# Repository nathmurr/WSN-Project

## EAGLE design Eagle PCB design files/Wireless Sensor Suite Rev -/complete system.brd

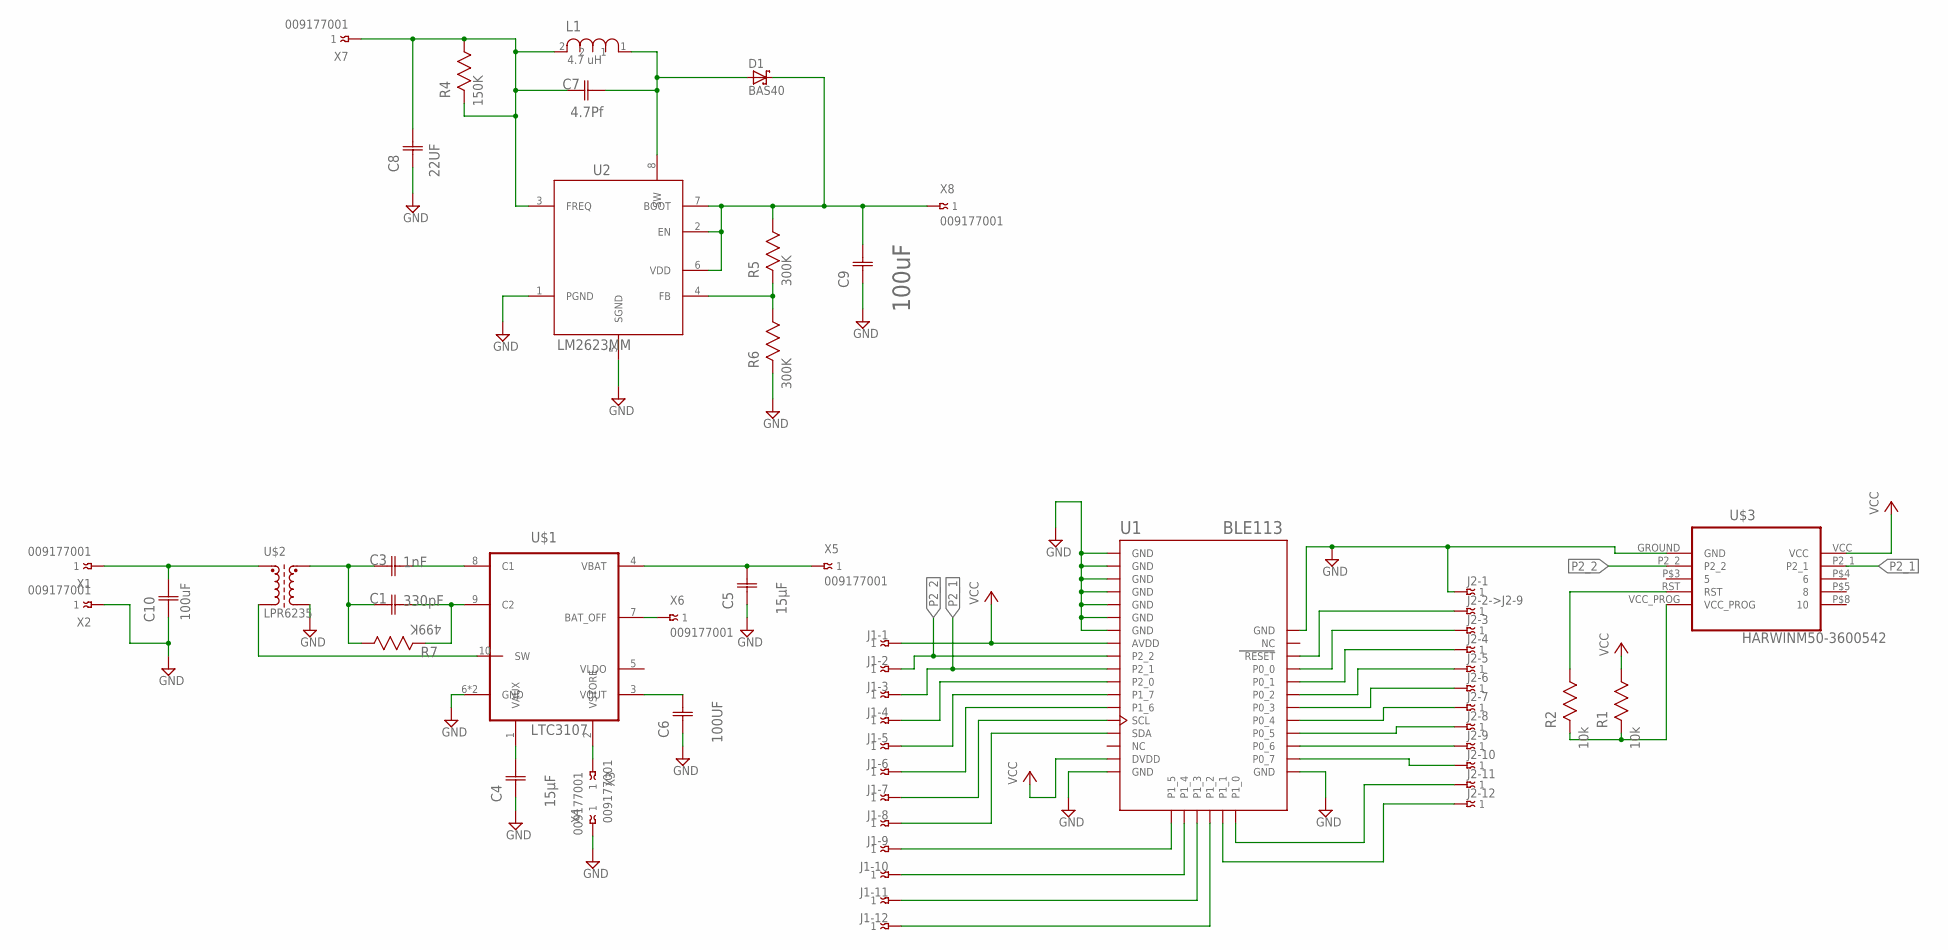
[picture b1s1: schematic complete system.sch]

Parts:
C1: 330pF; CAPC1005X60N
C3: 1nF; CAPC1005X60N
C4, C5: 15µF; CAPCP3216X180N
C6: 100UF; CAPCP3216X180N
C7: 4.7Pf; CAPC1005X60N
C8: 22UF; CAPC2012X94N
C9, C10: 100uF; CAPC3216X180N
D1: BAS40; SOT23
J1-1, J1-2, J1-3, J1-4, J1-5, J1-6, J1-7, J1-8, J1-9, J1-10, J1-11, J1-12, J2-1, J2-2->J2-9, J2-3, J2-4, J2-5, J2-6, J2-7, J2-8, J2-9, J2-10, J2-11, J2-12: 009177001
L1: 4.7 uH; INDC3225X22N
R1, R2: 10k; RESC1005X40N
R4: 150K; RESC1005X40N
R5, R6: 300K; RESC1005X40N
R7: 499K; RESC1005X40N
U1: BLE113; BLE113-A
U2: LM2623MM; SOP65P490X110-8N
U$1: LTC3107
U$2: LPR6235
U$3: HARWINM50-3600542
X1, X2, X3, X4, X5, X6, X7, X8: 009177001

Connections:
GND: C4.1 (C1), C5.1 (C1), C6.1 (C1), C8.1 (C1), C9.1 (C1), C10.1 (C1), J2-1.1, R6.2, U1.GND, U1.GND@2 (GND), U1.GND@3 (GND), U1.GND@4 (GND), U1.GND@5 (GND), U1.GND@6 (GND), U1.GND@7 (GND), U1.GND@8 (GND), U1.GND@9 (GND), U1.GND@10 (GND), U2.1 (PGND), U2.5 (SGND), U$1.6 (GND), U$1.11 (GND), U$2.P$3 (OP2), U$3.GROUND (GND), X2.1, X4.1
LL: J2-11.1, U1.P1_0
unnamed: C10.2 (C2), U$2.P$1 (IP1), X1.1
unnamed: U$1.10 (SW), U$2.P$2 (IP2)
unnamed: C1.1 (C2), R7.2, U$1.9 (C2)
unnamed: C1.2 (C1), C3.2 (C1), R7.1, U$2.P$4 (OP1)
unnamed: C3.1 (C2), U$1.8 (C1)
unnamed: C4.2 (C2), U$1.1 (VAUX)
unnamed: U$1.2 (VSTORE), X3.1
unnamed: C5.2 (C2), U$1.4 (VBAT), X5.1
unnamed: U$1.7 (BAT_OFF), X6.1
unnamed: C6.2 (C2), U$1.3 (VOUT)
unnamed: R1.2, R2.2, U$3.VCC_PROG
unnamed: R2.1, U$3.RST
unnamed: J1-4.1, U1.P2_0
unnamed: J1-5.1, U1.P1_7
unnamed: J1-6.1, U1.P1_6
unnamed: J1-7.1, U1.SCL
unnamed: J1-8.1, U1.SDA
unnamed: J1-9.1, U1.P1_5
unnamed: J1-10.1, U1.P1_4
unnamed: J1-11.1, U1.P1_3
unnamed: J1-12.1, U1.P1_2
unnamed: J2-3.1, U1.P0_0
unnamed: J2-4.1, U1.P0_1
unnamed: J2-2->J2-9.1, U1.RESET
unnamed: J2-5.1, U1.P0_2
unnamed: J2-6.1, U1.P0_3
unnamed: J2-7.1, U1.P0_4
unnamed: J2-8.1, U1.P0_5
unnamed: J2-9.1, U1.P0_6
unnamed: J2-10.1, U1.P0_7
unnamed: C7.1 (C2), D1.1 (A), L1.1, U2.8 (SW)
unnamed: J2-12.1, U1.P1_1
unnamed: C7.2 (C1), C8.2 (C2), L1.2, R4.1, R4.2, U2.3 (FREQ), X7.1
unnamed: C9.2 (C2), D1.3 (C), R5.1, U2.2 (EN), U2.6 (VDD), U2.7 (BOOT), X8.1
unnamed: R5.2, R6.1, U2.4 (FB)
P2_1: J1-3.1, U1.P2_1, U$3.P2_1
P2_2: J1-2.1, U1.P2_2, U$3.P2_2
VCC: J1-1.1, R1.1, U1.AVDD, U1.DVDD, U$3.VCC

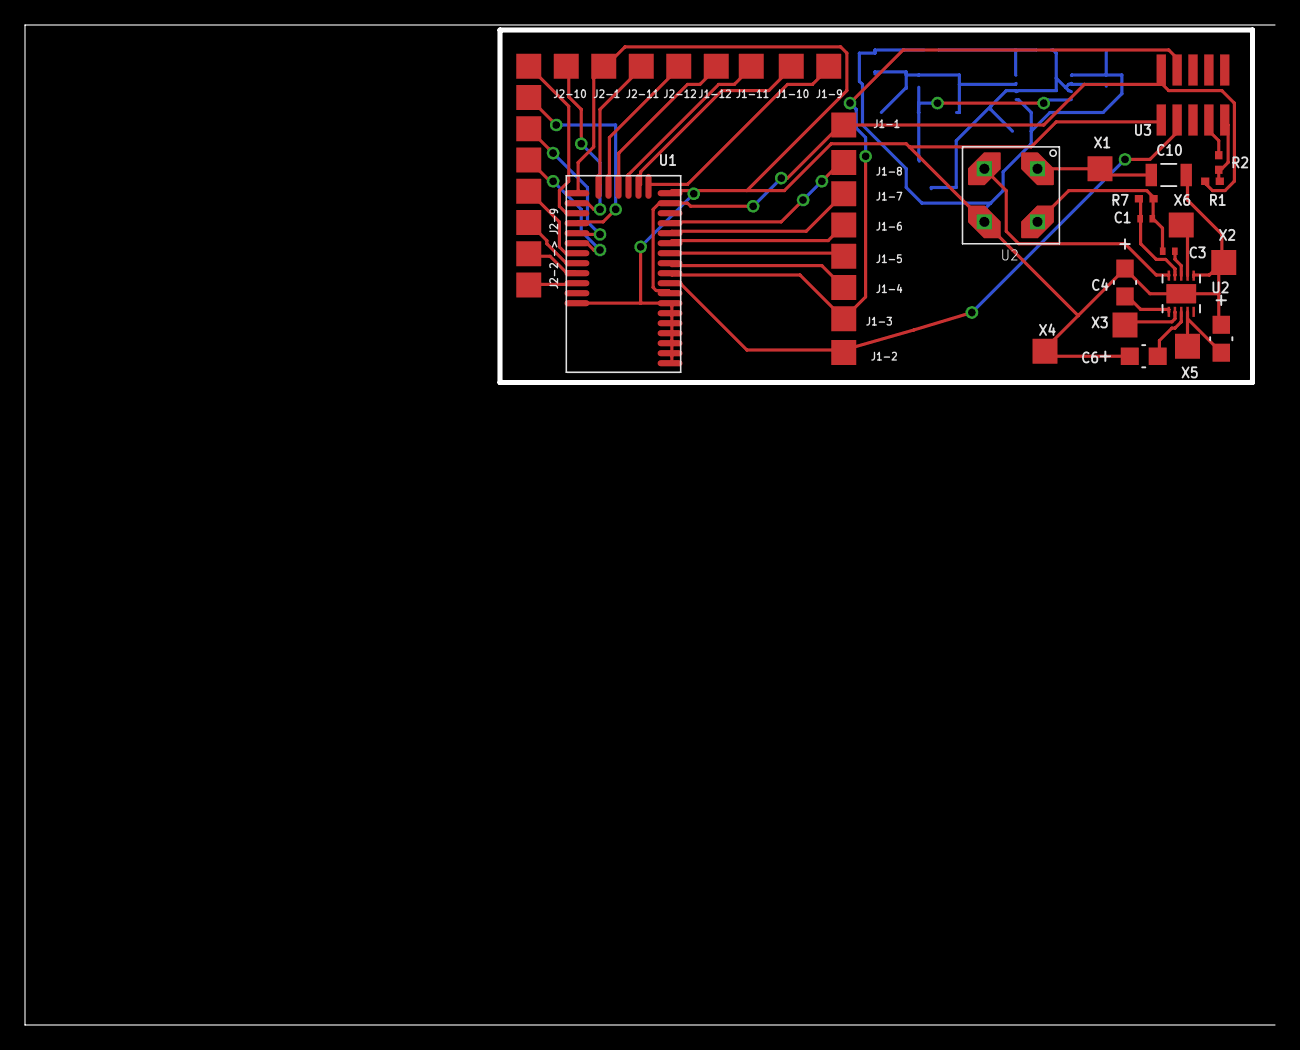
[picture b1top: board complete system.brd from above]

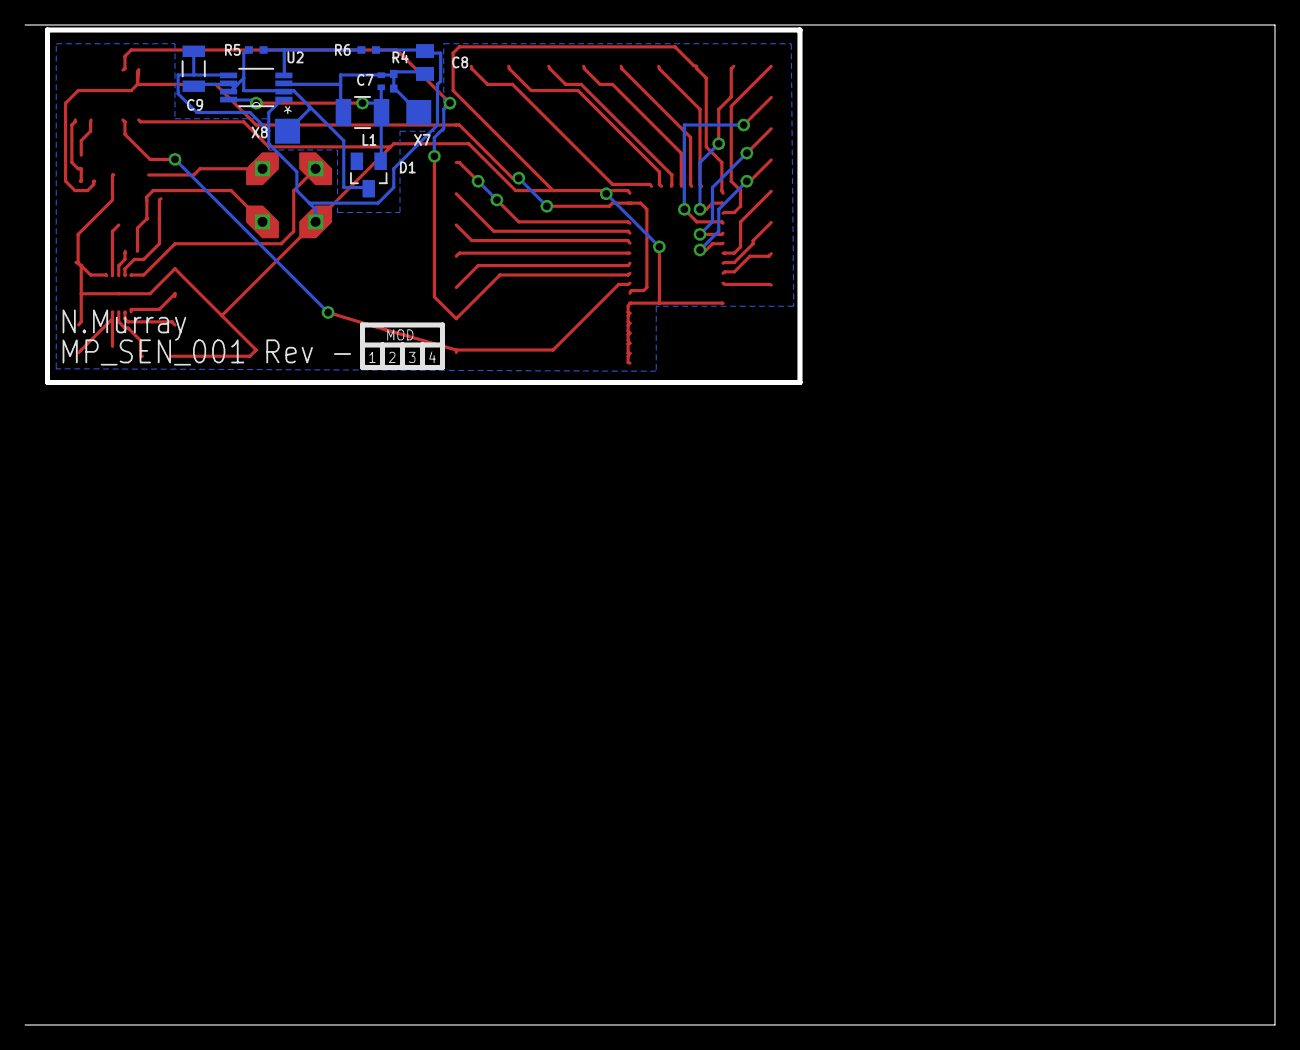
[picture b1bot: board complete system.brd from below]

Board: 2 copper layers, 99.6 x 79.6 mm, 54 parts (11 on the bottom side), 40 nets.

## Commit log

2015-08-31 All Project Files
    All project files for nm00169 dissertation
